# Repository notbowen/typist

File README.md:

# Sweep-style split keyboard

One reversible PCB (order one design, flip a board for the right half) for a wireless 34-key split that keeps the Ferris Sweep 2
shape (key positions and outline from the open-source
[Sweep](https://github.com/davidphilipbarr/Sweep), Solderpad Hardware License 2.1),
with a Seeed XIAO nRF52840 per half, 4 status LEDs per half, a plug-in LiPo cell under the controller,
Choc v1 hotswap sockets (Kailh Choc Sunset switches, blank white MBK caps) and ZMK firmware. No case:
the bare board stands on rubber feet. Comes with a headless design-and-verify toolchain.

**Live viewer: <https://notbowen.github.io/typist/>** — the current interactive 3D render of both
halves with the spec sheet, BOM and build guide ([`index.html`](index.html), served by GitHub Pages).

```sh
make setup   # toolchain: Python venv, ergogen, KiCad 9 + JRE docker images, Freerouting
make all     # layout -> PCB (DRC, plots)
make fab     # build/fab/sweep-gerbers.zip for JLCPCB (2 layers, 1.6 mm; 5 boards = 2 keyboards)
make viewer  # interactive 3D model of both halves + spec sheet, BOM, build guide (index.html)
```

- `ergogen/config.yaml` — key layout, board outlines, footprints and nets
- `pcb/` — hand-edited / routed boards (take precedence over generated ones)
- `scripts/` — KiCad wrappers, routing, DRC gate, plots, fab outputs, viewer
- `firmware/zmk-config/` — ZMK shield (`sweep_xiao_left` / `_right`) and starter keymap

See [CLAUDE.md](CLAUDE.md) for the pipeline, outputs and gotchas.

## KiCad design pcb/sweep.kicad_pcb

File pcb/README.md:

The routed, committed board lives here as `sweep.kicad_pcb` (one reversible PCB: the
right half is the same board flipped). When present it replaces
`build/ergogen/pcbs/sweep.kicad_pcb` in every make target.

It is `make route SIDE=sweep` output (Freerouting, then GND pours on both layers) with the
GND pours removed again: the board is black-core FR-4 under a clear mask, and only tracks
should show. GND is fully routed as tracks, so the pours were never needed for connectivity.
If you change placement in `ergogen/config.yaml`, re-run `make route SIDE=sweep` and
copy `build/pcb/sweep-routed.kicad_pcb` here again; ergogen output is unrouted.

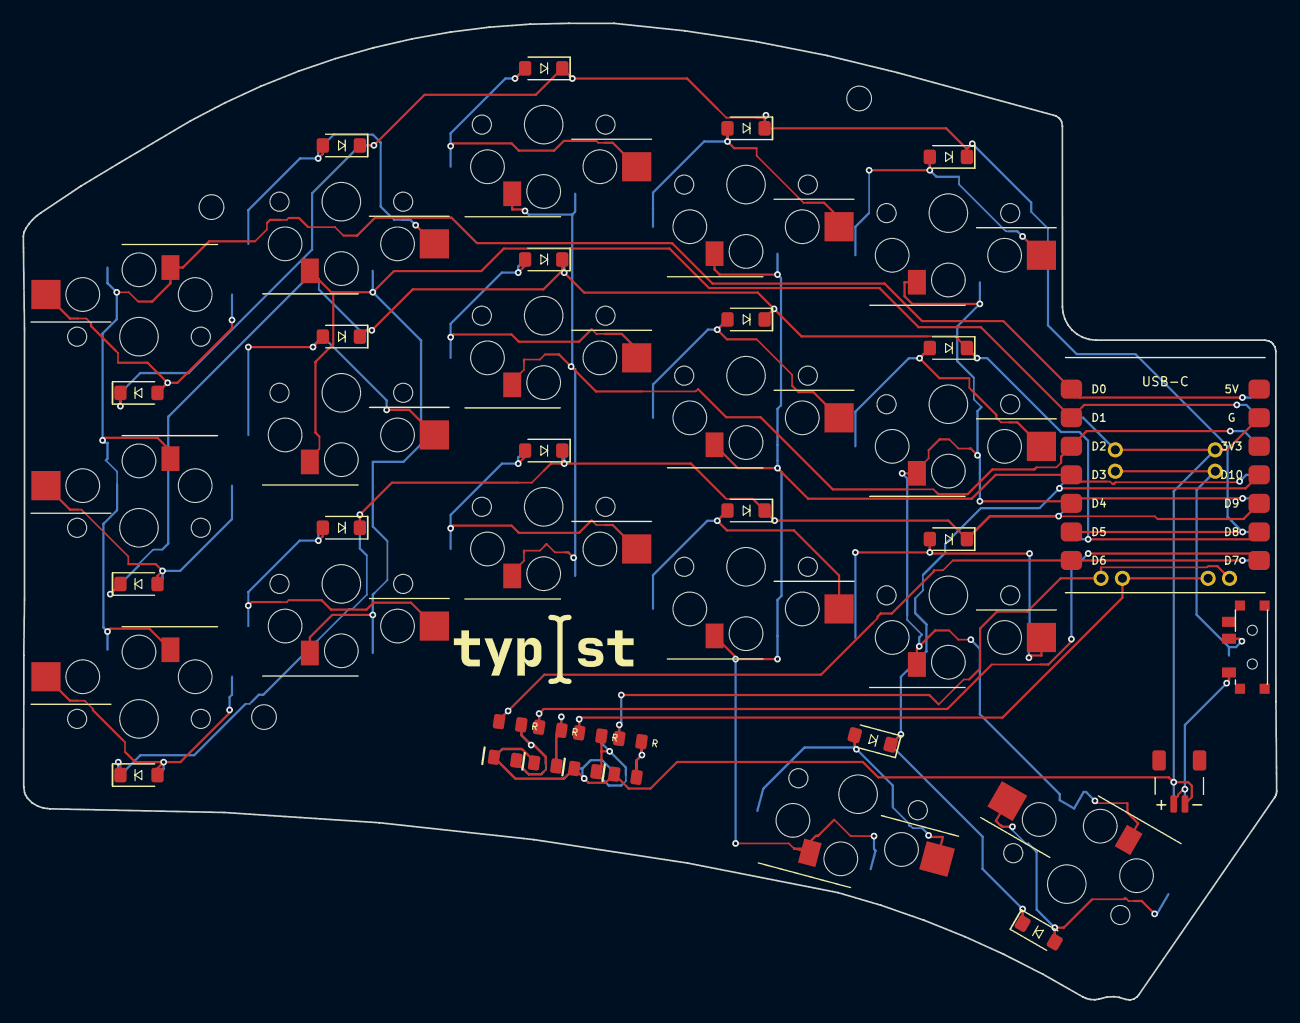
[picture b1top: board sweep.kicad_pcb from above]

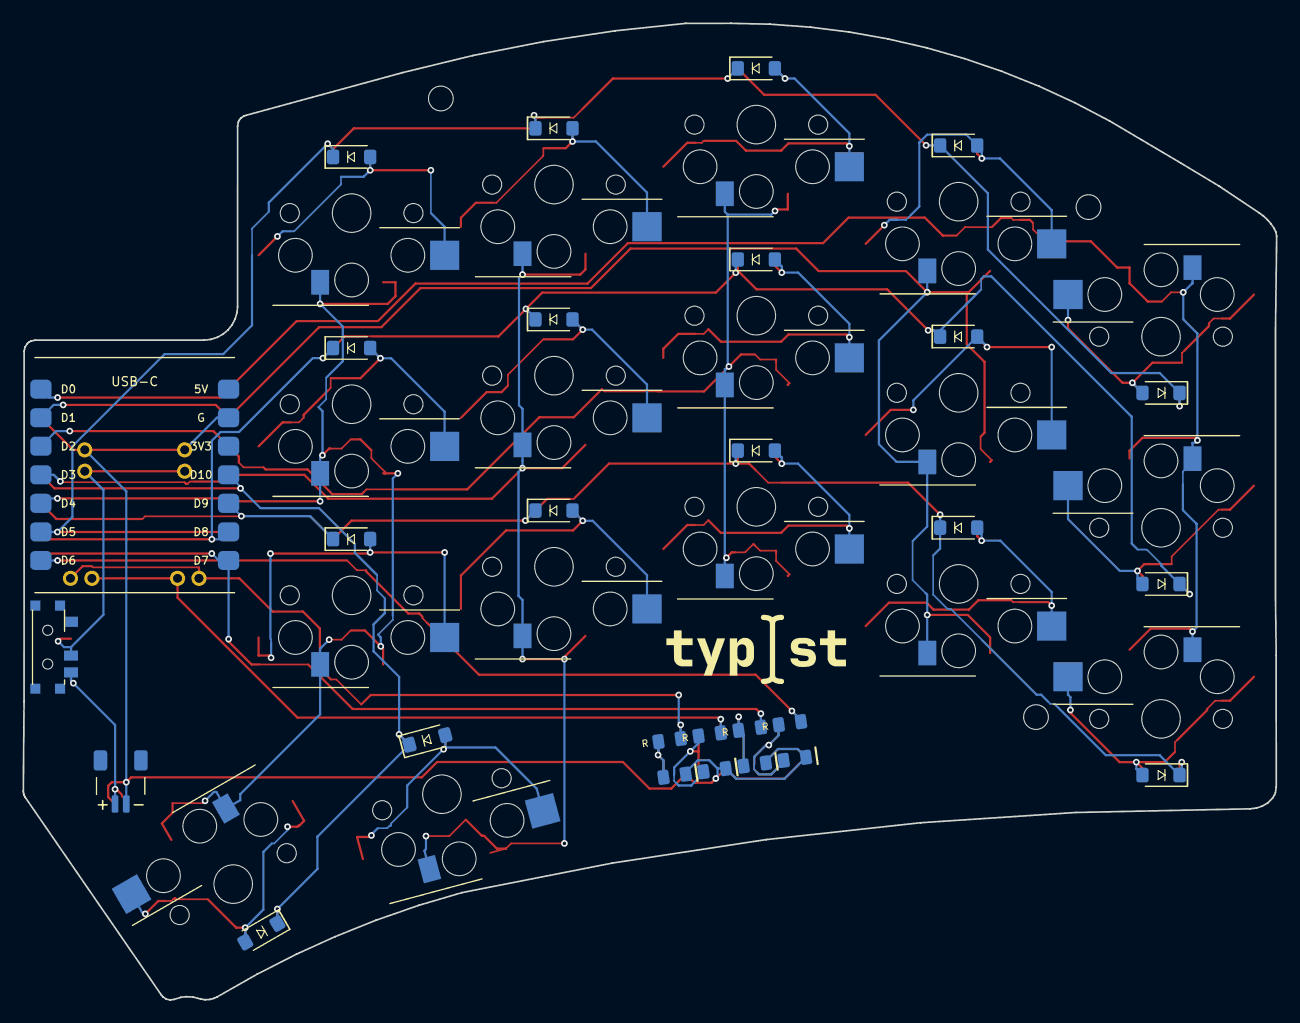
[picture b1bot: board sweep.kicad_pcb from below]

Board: 2 copper layers, 111.5 x 86.9 mm, 44 parts (18 on the bottom side), 37 nets.

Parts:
D1, D2, D3, D4, D5, D6, D7, D8, D9, D10, D11, D12, D13, D14, D15, D16, D17: 1N4148W; D_SOD-123
H1, H2, H3: MountingHole_NPTH
J1: SM02B-SRSS-TB; JST_SH_SM02B-SRSS-TB
LED1, LED2, LED3, LED4: LED_0805_R_0805_REV
MCU1: XIAO_nRF52840; XIAO_nRF52840_SMD_REV
S1, S2, S3, S4, S5, S6, S7, S8, S9, S10, S11, S12, S13, S14, S15, S16, S17: CHOC_V1_HOTSWAP_REV
SW1: MSK12C02_REV

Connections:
BAT_RAW: J1.1, SW1.1, SW1.3
BAT_SW: MCU1.16, SW1.2
C0: MCU1.1, S1.1, S2.1, S3.1
C1: MCU1.2, S5.1, S6.1, S7.1
C2: MCU1.3, S8.1, S9.1, S10.1
C3: MCU1.4, S11.1, S12.1, S13.1, S17.1
C4: MCU1.5, S4.1, S14.1, S15.1, S16.1
GND: J1.2, LED1.4, LED2.4, LED3.4, LED4.4, MCU1.9, MCU1.15
LED1: LED1.1, MCU1.7
LED1_A: LED1.2, LED1.3
LED2: LED2.1, MCU1.14
LED2_A: LED2.2, LED2.3
LED3: LED3.1, MCU1.17
LED3_A: LED3.2, LED3.3
LED4: LED4.1, MCU1.18
LED4_A: LED4.2, LED4.3
R0: D3.1, D7.1, D10.1, D13.1, D16.1, MCU1.6
R1: D2.1, D6.1, D9.1, D12.1, D15.1, MCU1.13
R2: D1.1, D5.1, D8.1, D11.1, D14.1, MCU1.12
R3: D4.1, D17.1, MCU1.11
matrix_index_bottom: D11.2, S11.2
matrix_index_home: D12.2, S12.2
matrix_index_top: D13.2, S13.2
matrix_inner_bottom: D14.2, S14.2
matrix_inner_home: D15.2, S15.2
matrix_inner_top: D16.2, S16.2
matrix_middle_bottom: D8.2, S8.2
matrix_middle_home: D9.2, S9.2
matrix_middle_top: D10.2, S10.2
matrix_pinky_bottom: D1.2, S1.2
matrix_pinky_home: D2.2, S2.2
matrix_pinky_top: D3.2, S3.2
matrix_ring_bottom: D5.2, S5.2
matrix_ring_home: D6.2, S6.2
matrix_ring_top: D7.2, S7.2
thumb_reachy_cluster: D4.2, S4.2
thumb_tucky_cluster: D17.2, S17.2

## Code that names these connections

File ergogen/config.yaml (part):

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# - 4x5 diode matrix: columns C0..C4 (pinky..inner) = D0..D4,
#   rows R0..R3 (top, home, bottom, thumb) = D5, D8, D9, D10
# - 4 status LEDs (0805 + 0805 resistor): LED1 = D6, LED2 = D7, LED3 = P0.09 (NFC1),
#   LED4 = P0.10 (NFC2) - every XIAO GPIO is used
# - LiPo on a JST-SH plug (bottom face), side power switch, no TRRS (ZMK BLE split)
# All coordinates mirror the reference: ergogen (x, y) == KiCad (x, -y).
meta:
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          row_net: R0
    thumb:
      anchor:
        ref: matrix_pinky_bottom
        shift: [63.97, -6.7]
        rotate: -15
      key:
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  board:
    - what: polygon
      points:
        - ref: matrix_pinky_bottom
          shift: [-10.222, 43.296]
          resist: true
        - shift: [-0.066, -0.37]
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          to: "{{row_net}}"
      hole1:
        what: mounting_hole
        where: matrix_pinky_bottom
        adjust:
          shift: [64.062, 55.188]
      hole2:
        what: mounting_hole
        where: matrix_pinky_bottom
        adjust:
          shift: [6.449, 45.528]    # Sweep hole moved 0.8 mm: a 4 mm hex standoff clears the ring-top socket
      hole3:
        what: mounting_hole
        where: matrix_pinky_bottom
        adjust:
          shift: [11.123, 0.162]    # Sweep hole moved 0.9 mm: clears the pinky-bottom socket
      led1:
        what: led_0805
        where: matrix_pinky_bottom
        adjust:
          shift: [led_x - 1.5 * led_dx, led_y - 1.5 * led_dy]
          rotate: led_rot
        params:
          gpio: LED1
          mid: LED1_A
          gnd: GND
      led2:
        what: led_0805
        where: matrix_pinky_bottom
        adjust:
          shift: [led_x - 0.5 * led_dx, led_y - 0.5 * led_dy]
          rotate: led_rot
        params:
          gpio: LED2
          mid: LED2_A
          gnd: GND
      led3:
        what: led_0805
        where: matrix_pinky_bottom
        adjust:
          shift: [led_x + 0.5 * led_dx, led_y + 0.5 * led_dy]
          rotate: led_rot
        params:
          gpio: LED3
          mid: LED3_A
          gnd: GND
      led4:
        what: led_0805
        where: matrix_pinky_bottom
        adjust:
          shift: [led_x + 1.5 * led_dx, led_y + 1.5 * led_dy]
          rotate: led_rot
        params:
          gpio: LED4
          mid: LED4_A
          gnd: GND
      mcu:
        what: xiao_nrf52840
        where: matrix_pinky_bottom
        adjust:
          shift: [mcu_x, mcu_y]
        params:
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          BATN: GND
      power:
        what: power_switch_rev
        where: matrix_pinky_bottom
        adjust:
          shift: [pwr_x, pwr_y]
          rotate: pwr_rot
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          to: BAT_SW
      battery:
        what: jst_sh2
        where: matrix_pinky_bottom
        adjust:
          shift: [jst_x, jst_y]
          rotate: jst_rot
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

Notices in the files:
ergogen/config.yaml:
(github.com/davidphilipbarr/Sweep, Solderpad Hardware License 2.1); pinky edge,
inner notch and controller tab grown ~2 mm for the double-sided hotswap pads
